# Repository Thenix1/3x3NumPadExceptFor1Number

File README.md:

# 3x3NumPadExceptFor1Number
This is a 3x3 pad, specifically for my use numpad, without one number, yeah... Cuz I realized that later on, but anyways, it doesn't do much. It kinda lives, kinda. It can type numbers. Soo yeah. First project, so don't judge 
# CAD model
The model consists of 2 parts, the bottom one, which is the bottom of the project and the top one which holds everzthing in place.
Everything's 3D printed, made in Autodesk Fusion.

# PCB model
Everything made in KiCAD 10, done by following the tutorial
Scheme

The actual design

Rotated the microcontroller for some reason :d

# Firmware
Used all QMK, well there wasn't much, just 9 keys

# BOM
Parts used:
9x Cherry MX Switches
9x DSA Keycaps
9x 1N4148 DO-35 Diodes
1x XIAO RP2040
1x Case (2 printed parts)
4x Some screws, idk what kind, just the fitting ones, ykyk.
4x Mb some heatset inserts so screws will hold, but still don't know what ones.

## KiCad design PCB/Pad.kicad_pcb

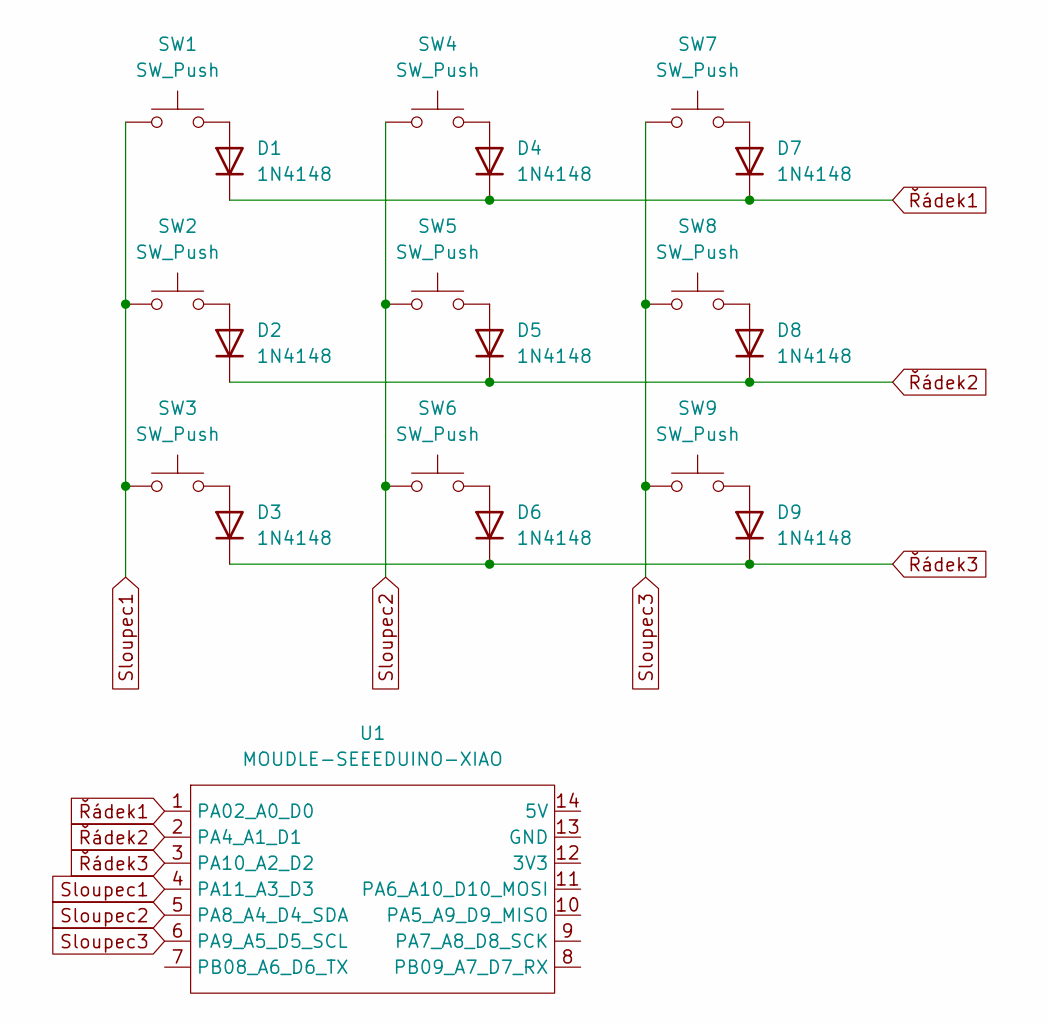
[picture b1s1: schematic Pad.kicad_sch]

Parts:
D1, D2, D3, D4, D5, D6, D7, D8, D9: 1N4148; D_DO-35_SOD27_P7.62mm_Horizontal
SW1, SW2, SW3, SW4, SW5, SW6, SW7, SW8, SW9: SW_Push; SW_Cherry_MX_1.00u_PCB
U1: MOUDLE-SEEEDUINO-XIAO; XIAO-Generic-Hybrid-14P-2.54-21X17.8MM

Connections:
unnamed: D1.2 (A), SW1.2
unnamed: D2.2 (A), SW2.2
unnamed: D3.2 (A), SW3.2
unnamed: D4.2 (A), SW4.2
unnamed: D5.2 (A), SW5.2
unnamed: D6.2 (A), SW6.2
unnamed: D7.2 (A), SW7.2
unnamed: D8.2 (A), SW8.2
unnamed: D9.2 (A), SW9.2
Sloupec1: SW1.1, SW2.1, SW3.1, U1.4 (PA11_A3_D3)
Sloupec2: SW4.1, SW5.1, SW6.1, U1.5 (PA8_A4_D4_SDA)
Sloupec3: SW7.1, SW8.1, SW9.1, U1.6 (PA9_A5_D5_SCL)
Řádek1: D1.1 (K), D4.1 (K), D7.1 (K), U1.1 (PA02_A0_D0)
Řádek2: D2.1 (K), D5.1 (K), D8.1 (K), U1.2 (PA4_A1_D1)
Řádek3: D3.1 (K), D6.1 (K), D9.1 (K), U1.3 (PA10_A2_D2)

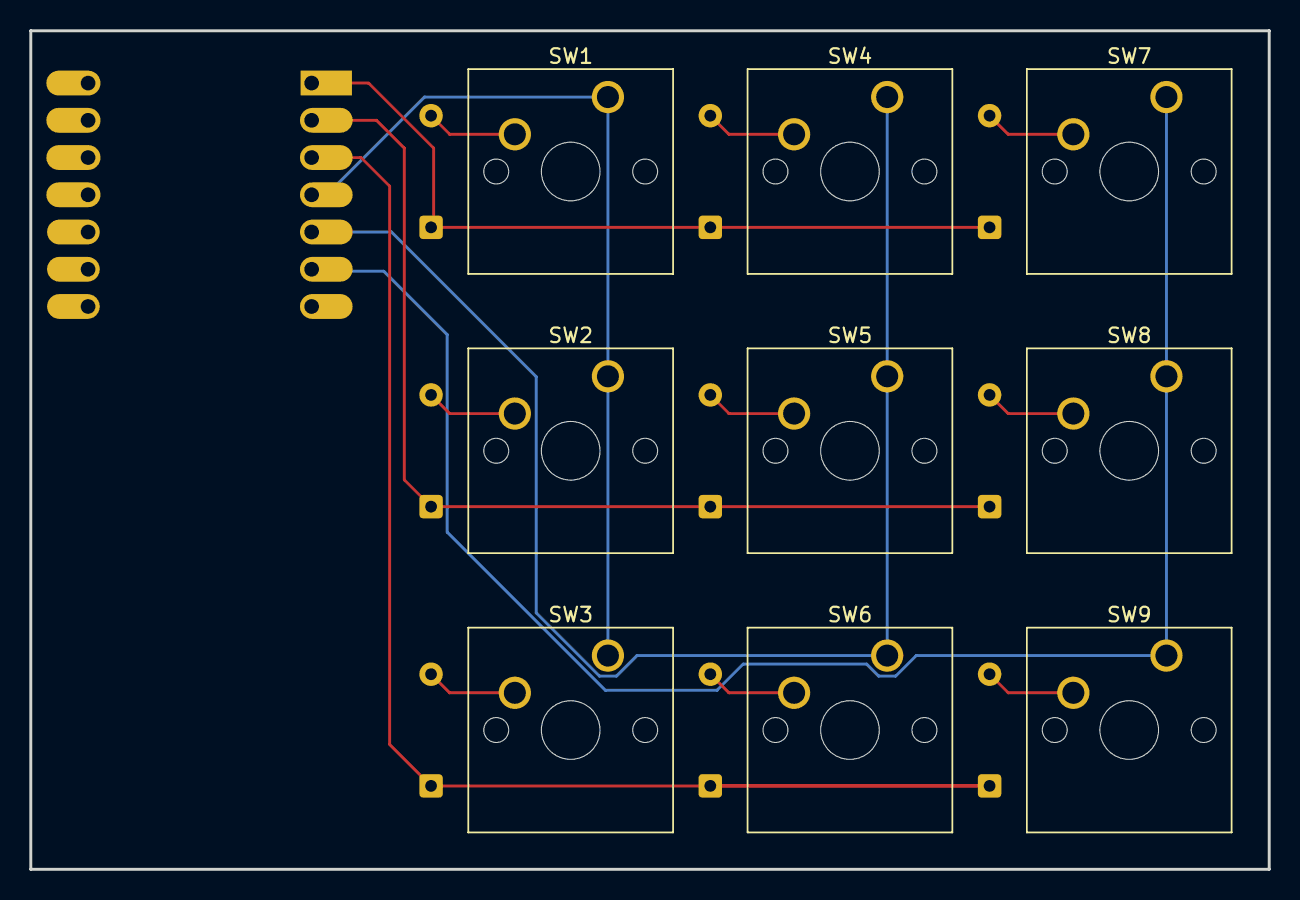
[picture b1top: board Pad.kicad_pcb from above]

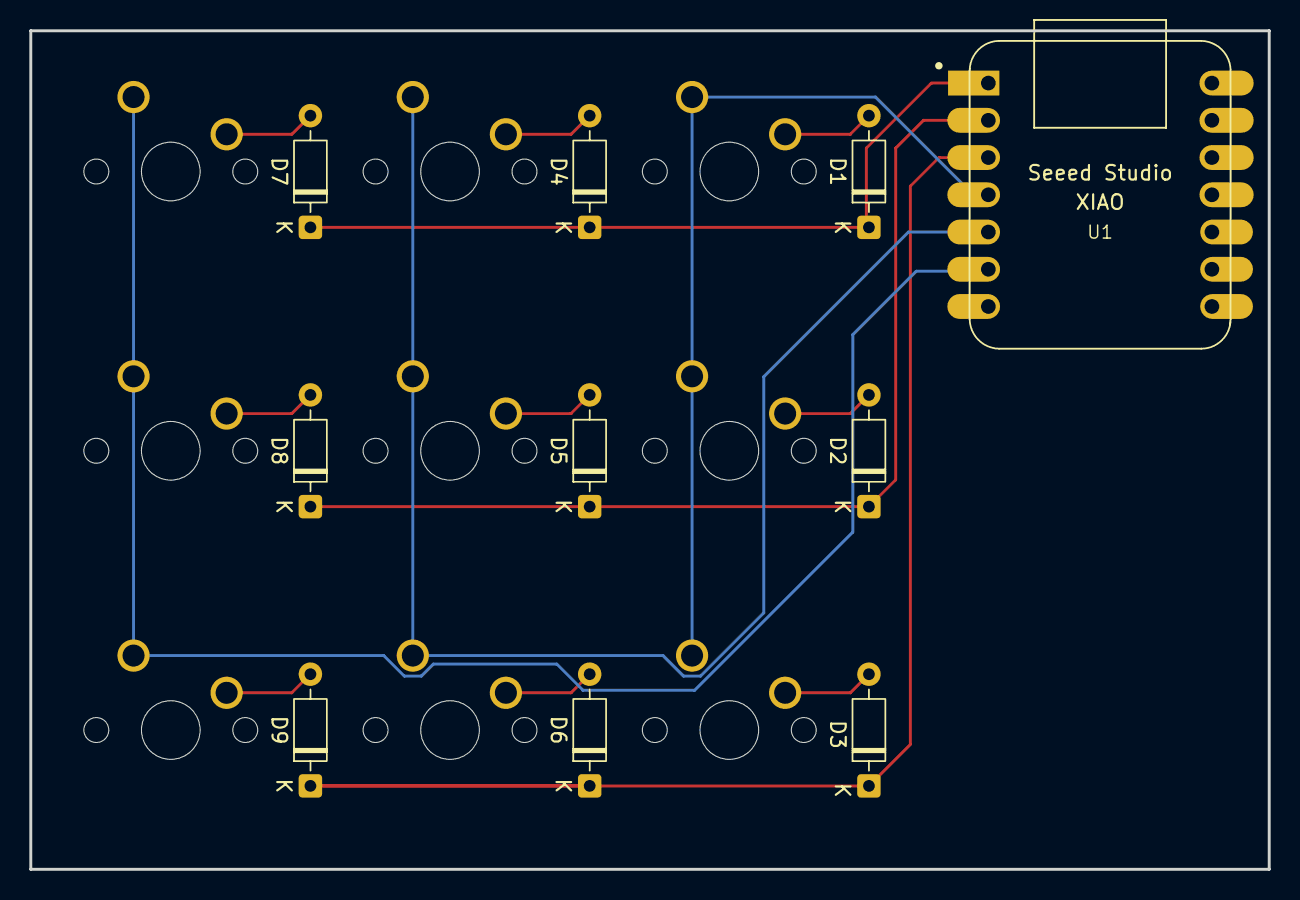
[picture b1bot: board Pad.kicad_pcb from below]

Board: 2 copper layers, 84.5 x 57.2 mm, 19 parts (10 on the bottom side), 15 nets.

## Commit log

2026-03-26 Create PCB
2026-03-26 Create dum
2026-03-26 Create mud
2026-03-26 Create jum
2026-03-26 Create m
